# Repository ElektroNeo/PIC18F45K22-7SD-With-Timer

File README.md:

# PIC18F45K22-7SD-With-Timer
7-Segment Display usage with PIC18F45K22 using timer interrupt.

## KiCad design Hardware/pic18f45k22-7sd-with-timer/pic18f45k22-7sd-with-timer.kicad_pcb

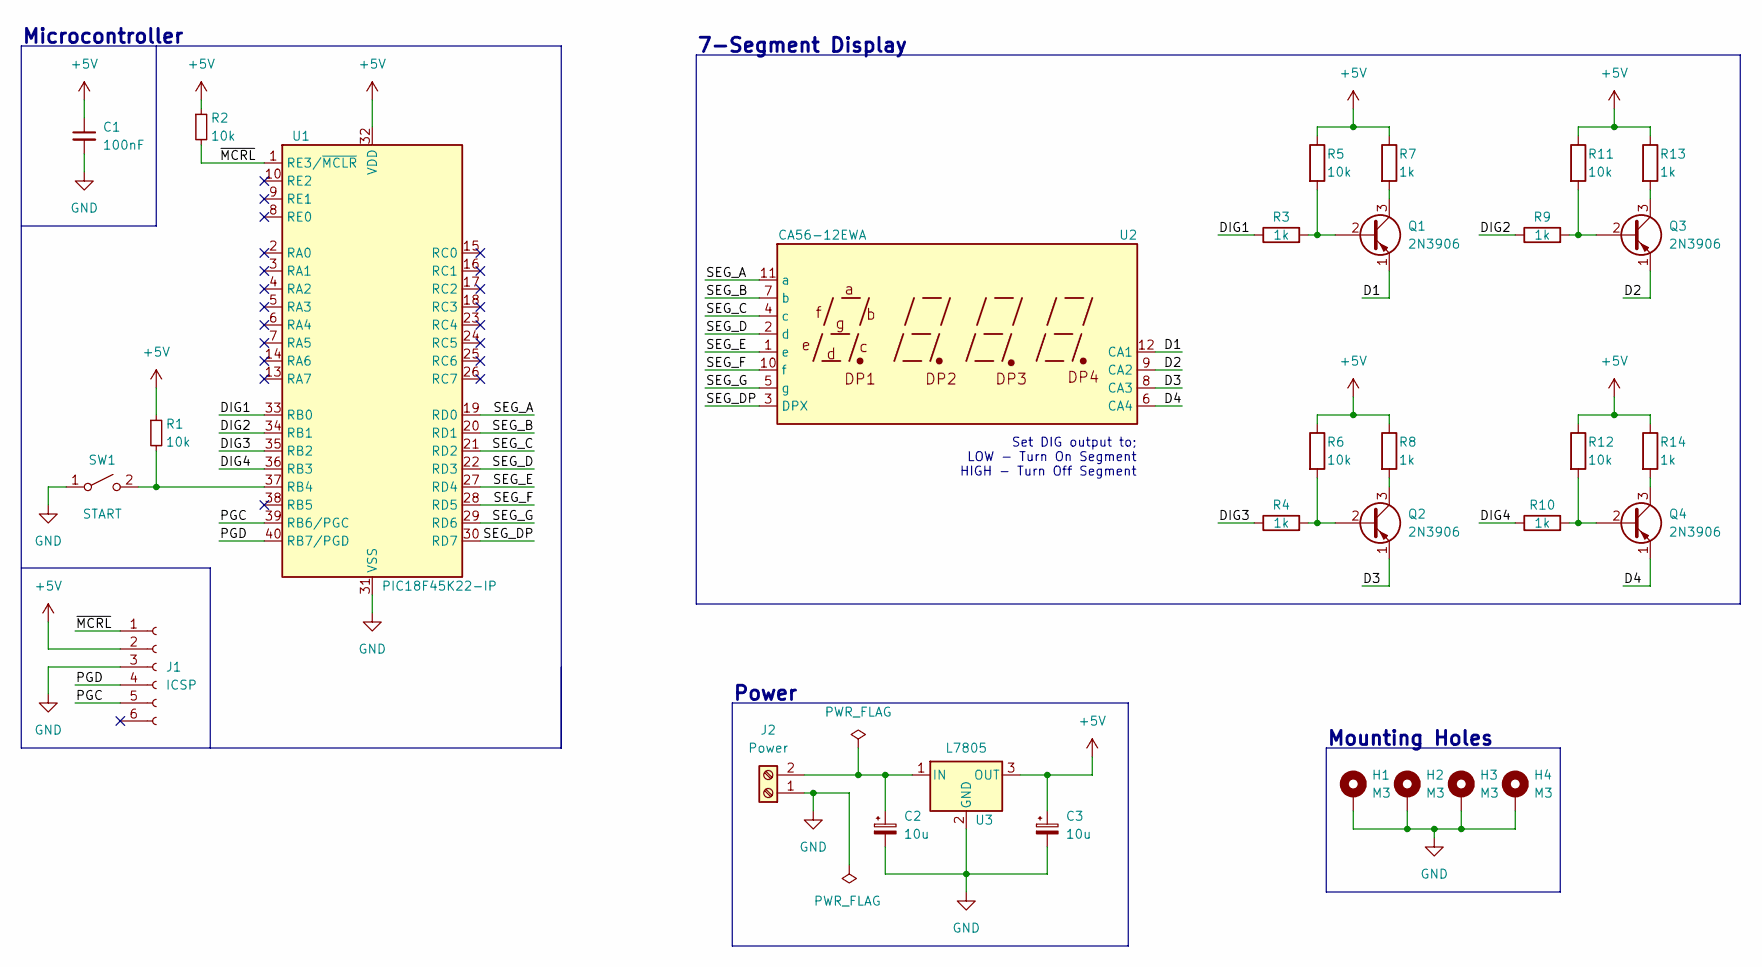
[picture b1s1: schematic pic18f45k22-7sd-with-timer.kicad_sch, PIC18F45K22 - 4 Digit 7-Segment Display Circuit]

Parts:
C1: 100nF; C_Disc_D3.8mm_W2.6mm_P2.50mm
C2, C3: 10u; CP_Radial_D5.0mm_P2.50mm
H1, H2, H3, H4: M3; MountingHole_3.2mm_M3_Pad_Via
J1: ICSP; PinHeader_1x06_P2.54mm_Vertical
J2: Power; Altech_AK300_1x02_P5.00mm_45-Degree
Q1, Q2, Q3, Q4: 2N3906; TO-92_Inline
R1, R2, R5, R6, R11, R12: 10k; R_Axial_DIN0207_L6.3mm_D2.5mm_P10.16mm_Horizontal
R3, R4, R7, R8, R9, R10, R13, R14: 1k; R_Axial_DIN0207_L6.3mm_D2.5mm_P10.16mm_Horizontal
SW1: START; SW_PUSH_6mm_H7.3mm
U1: PIC18F45K22-IP; DIP-40_W15.24mm_Socket
U2: CA56-12EWA
U3: L7805; TO-220-3_Horizontal_TabDown

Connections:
+5V: C1.1, C3.1, J1.2, R1.1, R2.1, R5.1, R6.1, R7.1, R8.1, R11.1, R12.1, R13.1, R14.1, U1.32 (VDD), U3.3 (OUT)
/D1: Q1.1 (E), U2.12 (CA1)
/D2: Q3.1 (E), U2.9 (CA2)
/D3: Q2.1 (E), U2.8 (CA3)
/D4: Q4.1 (E), U2.6 (CA4)
/DIG1: R3.1, U1.33 (RB0)
/DIG2: R9.1, U1.34 (RB1)
/DIG3: R4.1, U1.35 (RB2)
/DIG4: R10.1, U1.36 (RB3)
/PGC: J1.5, U1.39 (RB6/PGC)
/PGD: J1.4, U1.40 (RB7/PGD)
/SEG_A: U1.19 (RD0), U2.11 (a)
/SEG_B: U1.20 (RD1), U2.7 (b)
/SEG_C: U1.21 (RD2), U2.4 (c)
/SEG_D: U1.22 (RD3), U2.2 (d)
/SEG_DP: U1.30 (RD7), U2.3 (DPX)
/SEG_E: U1.27 (RD4), U2.1 (e)
/SEG_F: U1.28 (RD5), U2.10 (f)
/SEG_G: U1.29 (RD6), U2.5 (g)
/~MCRL: J1.1, R2.2, U1.1 (RE3/~MCLR)
GND: C1.2, C2.2, C3.2, H1.1, H2.1, H3.1, H4.1, J1.3, J2.1, SW1.1 (A), U1.31 (VSS), U3.2 (GND)
unnamed: C2.1, J2.2, U3.1 (IN)
unnamed: Q1.2 (B), R3.2, R5.2
unnamed: Q1.3 (C), R7.2
unnamed: Q2.2 (B), R4.2, R6.2
unnamed: Q2.3 (C), R8.2
unnamed: Q3.2 (B), R9.2, R11.2
unnamed: Q3.3 (C), R13.2
unnamed: Q4.2 (B), R10.2, R12.2
unnamed: Q4.3 (C), R14.2
unnamed: R1.2, SW1.2 (B), U1.37 (RB4)

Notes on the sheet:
Microcontroller
7-Segment Display
Set DIG output to; LOW - Turn On Segment HIGH - Turn Off Segment
Mounting Holes
Power

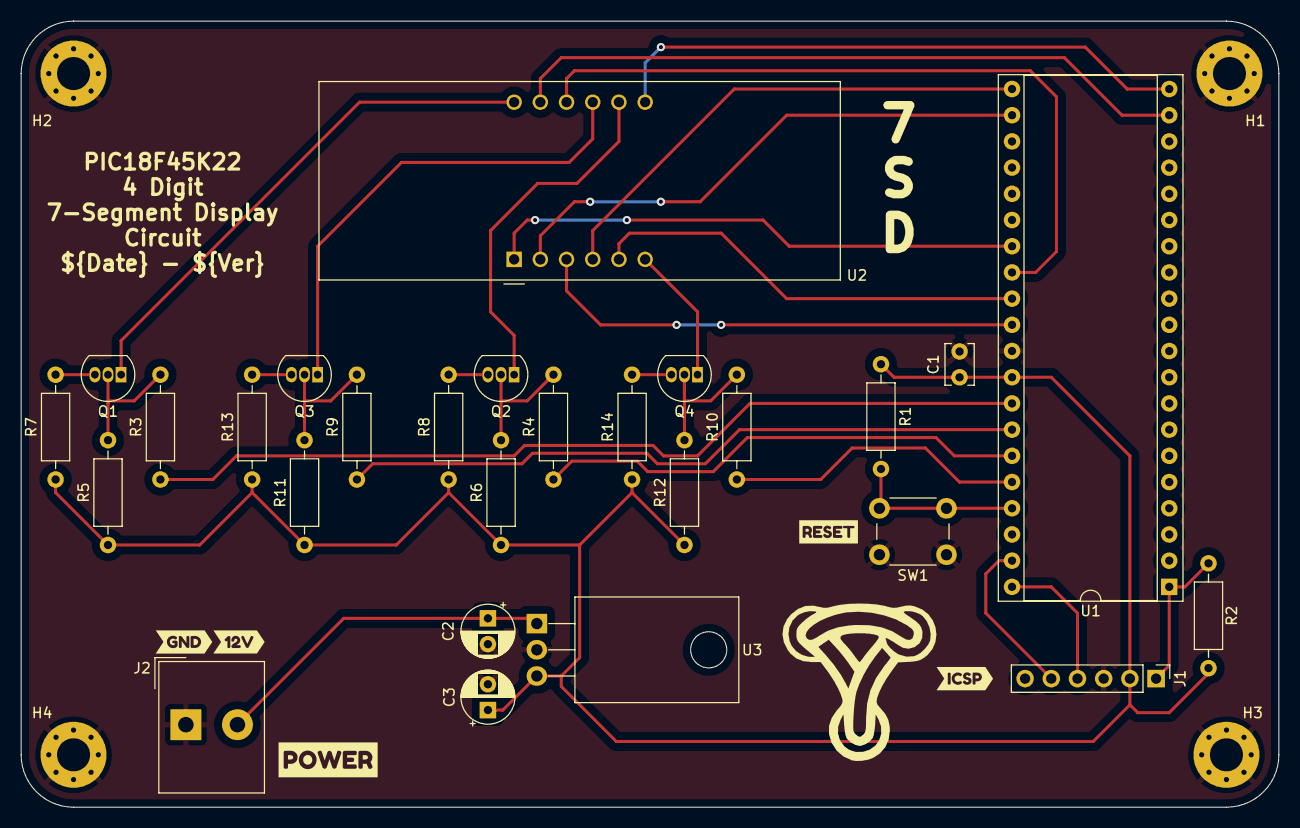
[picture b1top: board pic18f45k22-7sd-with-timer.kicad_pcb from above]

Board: 2 copper layers, 121.9 x 76.2 mm, 36 parts (0 on the bottom side), 31 nets.

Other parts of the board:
kibuzzard-62FBC8B8: G***; kibuzzard-62FBC8B8
kibuzzard-62FBC8C7: G***; kibuzzard-62FBC8C7
kibuzzard-62FBC8E2: G***; kibuzzard-62FBC8E2
kibuzzard-62FBC8F8: G***; kibuzzard-62FBC8F8
kibuzzard-62FBC81B: G***; kibuzzard-62FBC81B

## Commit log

2022-08-16 Added PCB design.
2022-10-09 Update.
2023-01-30 Ignore production and build files.
2023-01-30 Refactoring.
